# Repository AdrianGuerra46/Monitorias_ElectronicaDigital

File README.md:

# Monitoria Electrónica Digital 

### Docente: Yeison Montagut 

Seré el monitor (también conocido como asistente de docencia) de electrónica digital, asignatura de Séptimo semestre de Ingeniería Mecatrónica en la Universidad EIA. 

Mi responsabilidad directa será dar asesoria a los estudiantes en los eventos calificables los cuales son: exámenes (dos(2) quices, parcial y final) y los 3 últimos de los 4 laboratorios de la asignatura (no ayudaré de manera directa en el laboratorio 1 por solicitud del docente) aún asi, daré apoyo extra a los estudiantes si es necesario.  

***Aclaración:*** El equipo que uso para desarrollar todas las tareas funciona con el sistema operativo Windows. Por esta razón todo el desarrollo del repositorio y las diferentes recomendaciones estarán hechas desde mi experiencia abordando todo con Windows. AUN ASÍ el proceso no cambia en prácticamente nada desde otros sistemas operativos.
> **NOTA:** El objetivo del repositorio **NO** es exponer y explicar todo el temario de la asignatura. El objetivo es exponer la solución de los entregables y los diferentes desarrollos que llevé a cabo para poder afrontar mi rol de monitor de la mejor manera posible. 

#### Desarrollo de la asignatura 

De forma **muy general** la asignatura se divide principalmente en dos temas, los cuales están divididos cronológicamente por el examen parcial.

1. [**Pre-Parcial**](https://github.com/AdrianGuerra46/Monitorias_ElectronicaDigital/tree/main/Pre-Parcial): En esta primera parte tenemos el primer acercamiento a la electrónica digital trantando temas como:
    - Sistemas numéricos 
    - Compuertas lógicas
    - FPGA (Basys 3)
    - VHDL (Vivado)
    - Entre otros. 

    Esta primera parte incluye los siguientes eventos calificables:

    - Laboratorio 1: Primer acercamiento con la tarjeta Basys 3 y comprobación práctica de las compuertas lógicas usando el lenguaje VHDL y el software Vivado. 
    - Quiz 1: Enfocado en Compuertas lógicas y aplicación sobre la tarjeta Basys 3 usando VHDL.
    - Laboratorio 2: Diseñar e implementar sistemas digitales basado en lógica secuencial en una FPGA.
    - Parcial: Es la segunda evaluación más significativa del curso (con una valor del 20%) y se evaua todo el conocimiento tanto conceptual como práctico obtenido hasta el momento. 
2. [**Post-Parcial:**](https://github.com/AdrianGuerra46/Monitorias_ElectronicaDigital/tree/main/Post-Parcial) En esta segunda parte del curso nos enfocamos en microcontroladores y se abordan temas como: 
    - Introducción a los microcontroladores (Qué es?, Partes, entre otros.).
    - ESP32 (Principal microcontrolador de la asignatura) 
    - Visual Studio Code 
    - Manejo de Puertos
    - Sensores
    - Entre otros.

    En esta segunda parte de la asignatura tendremos los siguientes eventos calificables:
    - Laboratorio 3: Diseñar e implementar una aplicación básica en un microcontrolador ESP32.
    - Quiz 2: Enfocado en la programación de microncotroladores, trabajando sobre VSCode
    - Laboratorio 4: Implementar una aplicación completa sobre el microcontrolador ESP32. 
    - Final: Examen más importante de la asignatura (con un valor del 30%) donde se evaluará todo el conocimiento adquirido durante la asignatura aunque, enfocado principalmente en los temas Post-Parcial.

Cada uno de estos temas estarám mejor abordados en sus respectivos directorios

### Estructura del repositorio

- En el repositorio montaré todo lo que tenga que resolver/desarrollar durante el proceso de la monitoria, es decir, talleres, laboratorios, entre otros. 
- Dividiré el temario y desarrollo en dos directorios, Pre-Parcial y Post-Parcial. En los cuales abordaré todo los diseños y soluciones. Estarán divididos en tantos directorios y ficheros como considere necesarios (esto estará mejor explicado en el archivo README de cada directorio).
- A su vez, estos directorios estarán divididos en otros directorios los cuales estarán enumerados de forma cronológica (para ser abordados de la misma manera). En estos se encontrarán tanto enunciados como soluciones de cada Taller, Quiz, Laboratorio, Etc. 

> Nota: En algunos directorios puede que haya algunos archivos PDF provenientes de mi Tablet (dispositivo donde tomo apuntes) estos serán incluidos si condero necesario para realizar anotaciones o desarrolos más explicitos y dejar mejor explicado el tema o el el proceso de diseño de cada entregable. *De antemano me disculpo por mi letra y gráficos* :sweat_smile:

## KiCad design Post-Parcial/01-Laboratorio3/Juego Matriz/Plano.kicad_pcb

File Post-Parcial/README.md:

# Post-Parcial 

## Microcontroladores

La segunda mitad de la asignatura está enfocada principalmente en **microcontroladores**. El microcontrolador "rey de la asignatura" será el ESP32, sobre este desarrollaremos software para implementar en hardware. Programaremos en C y Arduino, para proximamente implementar en cirucitos haciendo uso desde led's hasta sensores y motores.

## Requisitos Previos

- **Visual Studio Code:** Visual Studio Code es un editor de código fuente desarrollado por Microsoft para Windows, Linux, macOS y Web. Este será nuestro editor de código en esta parte de la asignatura. Puedes descargarlo directamente desde su [sitio oficial](https://code.visualstudio.com/download).
    - PlatformIO: es una IDE abierta de programación para C/C++, orientado al hardware. ¿Qué es una IDE? Es una sigla y acrónimo en inglés de integrated development environment, en español es un conjunto de herramientas para desarrollo (programación) generalmente agrupadas en una misma interfaz gráfica. Este será el IDE que usaremos para programar el ESP32 tanto en C como en Arduino. Puedes decargarlo desde la interfaz de extensiones de Visual Studio Code. 

- **Driver:** Según mi experiencia algunos equipos pueden tener problemas para reconocer el ESP32. Esto puedes verlo accediendo al administrador de dispositivos e identificando un simbolo de exclamación sobre un dispositivo USB.
  
  Si ese llega a ser tu caso, puedes descargar el driver desde [Este enlace](https://www.silabs.com/developers/usb-to-uart-bridge-vcp-drivers?tab=downloads) Te recomiendo la versión "Universal Windows Driver" (Si estas trabajando desde Windows). E instalarlo dandole a "actualizar controlador" y buscando la carpeta donde descargaste el controlador.
- **Proteus:** Proteus es el programa con el que se realizarán algunas simulaciones de los circuitos electrónicos, procedimiento el cual siempre es recomendado antes de montar directaremente los componentes.
- **KiCad8:** Este es mi programa preferido para realizar esquematicos y migrarlos a PCB, y por esta razón lo usaré para realizar los esquematicos que considere necesarios (En la asignatura no se aborda directamente el diseño de PCB ni el uso de este software, esto es puramente elección personal). Puedes descargarlo desde su [página oficial](https://www.kicad.org/download/).

## Conceptos 

### ¿Qué es un microcontrolador?

Un microcontrolador (abreviado µC, UC o mCU) es un circuito integrado programable, capaz de ejecutar las órdenes grabadas en su memoria. Está compuesto de varios bloques funcionales que cumplen una tarea específica. Un microcontrolador incluye en su interior las tres principales unidades funcionales de una computadora: unidad central de procesamiento, memoria y periféricos de entrada/salida.

### ESP32

ESP32 es la denominación de una familia de chips SoC de bajo coste y consumo de energía, con tecnología Wi-Fi y Bluetooth de modo dual integrada. El ESP32 emplea un microprocesador Tensilica Xtensa LX6 en sus variantes de simple y doble núcleo e incluye interruptores de antena, balun de radiofrecuencia, amplificador de potencia, amplificador receptor de bajo ruido, filtros, y módulos de administración de energía. El ESP32 fue creado y desarrollado por Espressif Systems y es fabricado por TSMC utilizando su proceso de 40 nm.Este será nuestra principal herramienta de trabajo en esta segunda y última parte del curso.

##### Distribución de Pinout de ESP32

Esta imagen será muy importante para el desarrollo de todos los sistemas asociados a este microncontrolador.

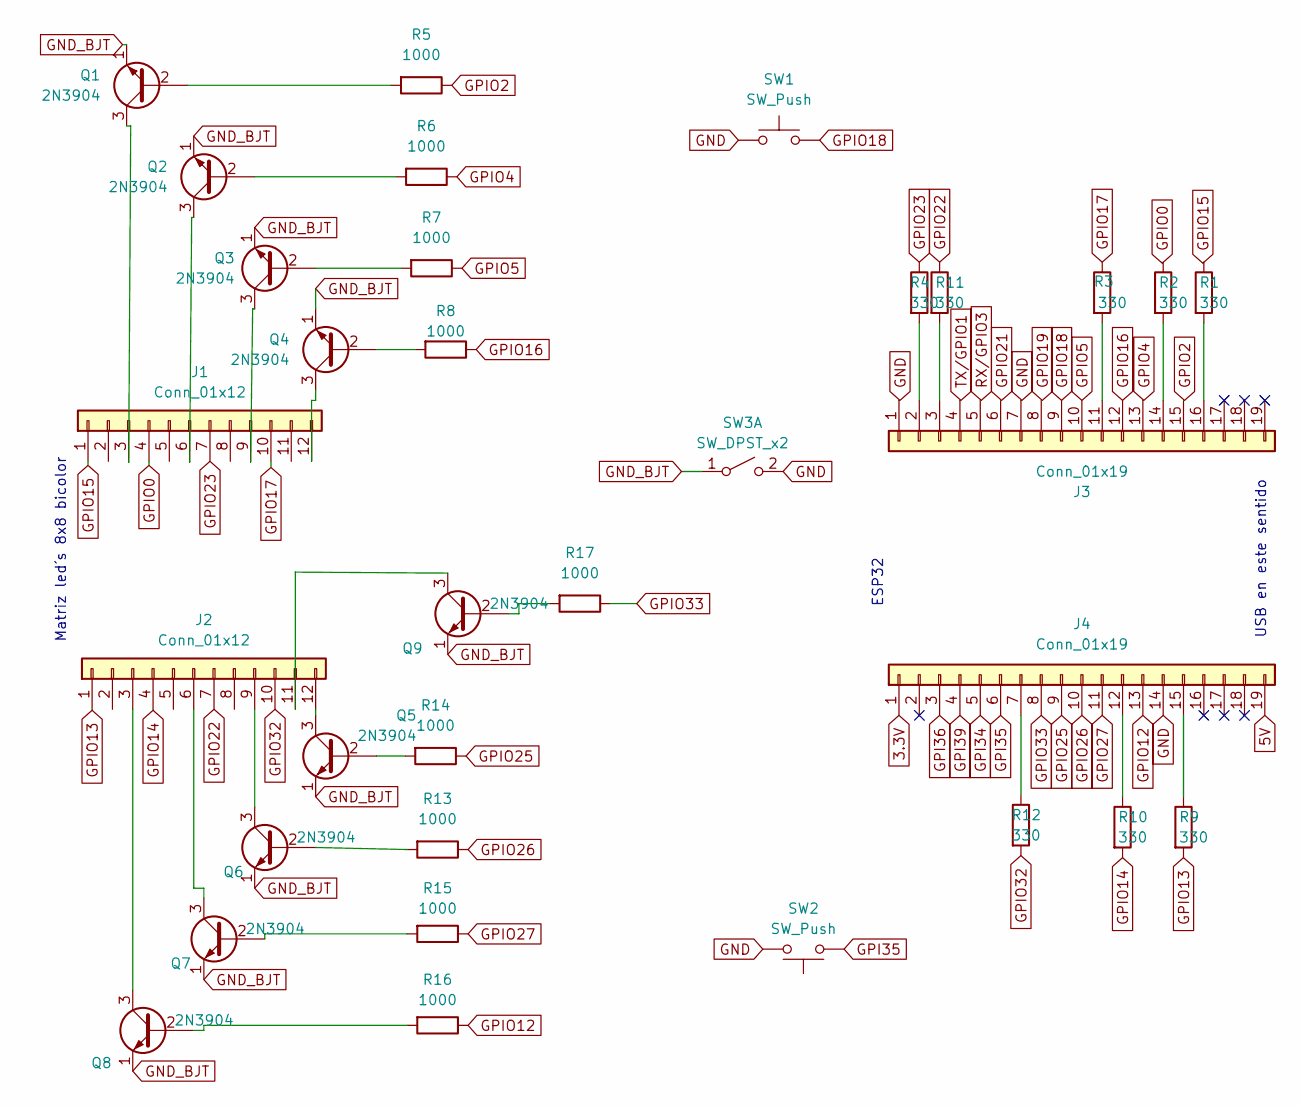
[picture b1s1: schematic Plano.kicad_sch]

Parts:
J1, J2: Conn_01x12; PinSocket_1x12_P2.54mm_Vertical
J3, J4: Conn_01x19; PinSocket_1x19_P2.54mm_Vertical
Q1, Q2, Q3, Q4, Q5, Q6, Q7, Q8, Q9: 2N3904; PinSocket_1x03_P2.54mm_Vertical
R1, R2, R3, R9, R10: 330; R_Axial_DIN0309_L9.0mm_D3.2mm_P2.54mm_Vertical
R4, R11, R12: 330; R_Axial_DIN0207_L6.3mm_D2.5mm_P10.16mm_Horizontal
R5, R6, R7, R8, R14, R15, R16, R17: 1000; R_Axial_DIN0309_L9.0mm_D3.2mm_P2.54mm_Vertical
R13: 1000; R_Axial_DIN0207_L6.3mm_D2.5mm_P10.16mm_Horizontal
SW1, SW2: SW_Push; SW_DIP_SPSTx01_Piano_10.8x4.1mm_W7.62mm_P2.54mm
SW3: SW_DPST_x2; SW_DIP_SPSTx01_Slide_6.7x4.1mm_W7.62mm_P2.54mm_LowProfile

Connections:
3.3V: J4.1
5V: J4.19
GND: J3.1, J3.7, J4.14, SW1.1, SW2.2, SW3.2 (B)
GND_BJT: Q1.1 (E), Q2.1 (E), Q3.1 (E), Q4.1 (E), Q5.1 (E), Q6.1 (E), Q7.1 (E), Q8.1 (E), Q9.1 (E), SW3.1 (A)
GPI34: J4.5
GPI35: J4.6, SW2.1
GPI36: J4.3
GPI39: J4.4
GPIO0: J1.4, R2.1
GPIO2: J3.15, R5.1
GPIO4: J3.13, R6.1
GPIO5: J3.10, R7.1
GPIO12: J4.13, R16.1
GPIO13: J2.1, R9.2
GPIO14: J2.4, R10.2
GPIO15: J1.1, R1.1
GPIO16: J3.12, R8.1
GPIO17: J1.10, R3.1
GPIO18: J3.9, SW1.2
GPIO19: J3.8
GPIO21: J3.6
GPIO22: J2.7, R11.1
GPIO23: J1.7, R4.1
GPIO25: J4.9, R14.1
GPIO26: J4.10, R13.1
GPIO27: J4.11, R15.1
GPIO32: J2.10, R12.2
GPIO33: J4.8, R17.1
unnamed: J1.3, Q1.3 (C)
unnamed: J1.6, Q2.3 (C)
unnamed: J1.9, Q3.3 (C)
unnamed: J1.12, Q4.3 (C)
unnamed: J2.3, Q8.3 (C)
unnamed: J2.6, Q7.3 (C)
unnamed: J2.9, Q6.3 (C)
unnamed: J2.11, Q9.3 (C)
unnamed: J2.12, Q5.3 (C)
unnamed: J3.2, R4.2
unnamed: J3.3, R11.2
unnamed: J3.11, R3.2
unnamed: J3.14, R2.2
unnamed: J3.16, R1.2
unnamed: J4.7, R12.1
unnamed: J4.12, R10.1
unnamed: J4.15, R9.1
unnamed: Q1.2 (B), R5.2
unnamed: Q2.2 (B), R6.2
unnamed: Q3.2 (B), R7.2
unnamed: Q4.2 (B), R8.2
unnamed: Q5.2 (B), R14.2
unnamed: Q6.2 (B), R13.2
unnamed: Q7.2 (B), R15.2
unnamed: Q8.2 (B), R16.2
unnamed: Q9.2 (B), R17.2
RX/GPIO3: J3.5
TX/GPIO1: J3.4

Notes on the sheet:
USB en este sentido
ESP32
Matriz led´s 8x8 bicolor

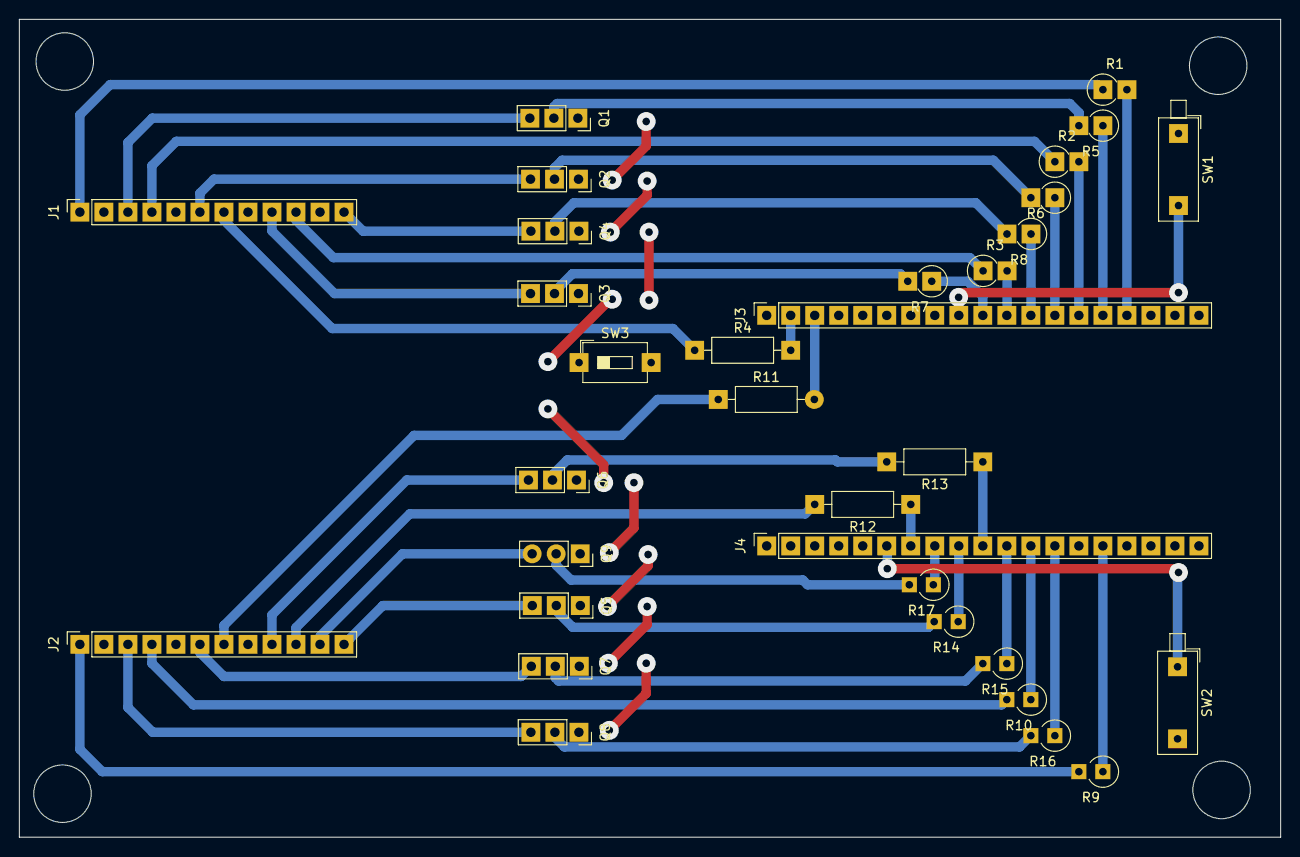
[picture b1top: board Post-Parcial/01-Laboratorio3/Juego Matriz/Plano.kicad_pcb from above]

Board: 2 copper layers, 133.4 x 86.5 mm, 33 parts (0 on the bottom side), 47 nets.

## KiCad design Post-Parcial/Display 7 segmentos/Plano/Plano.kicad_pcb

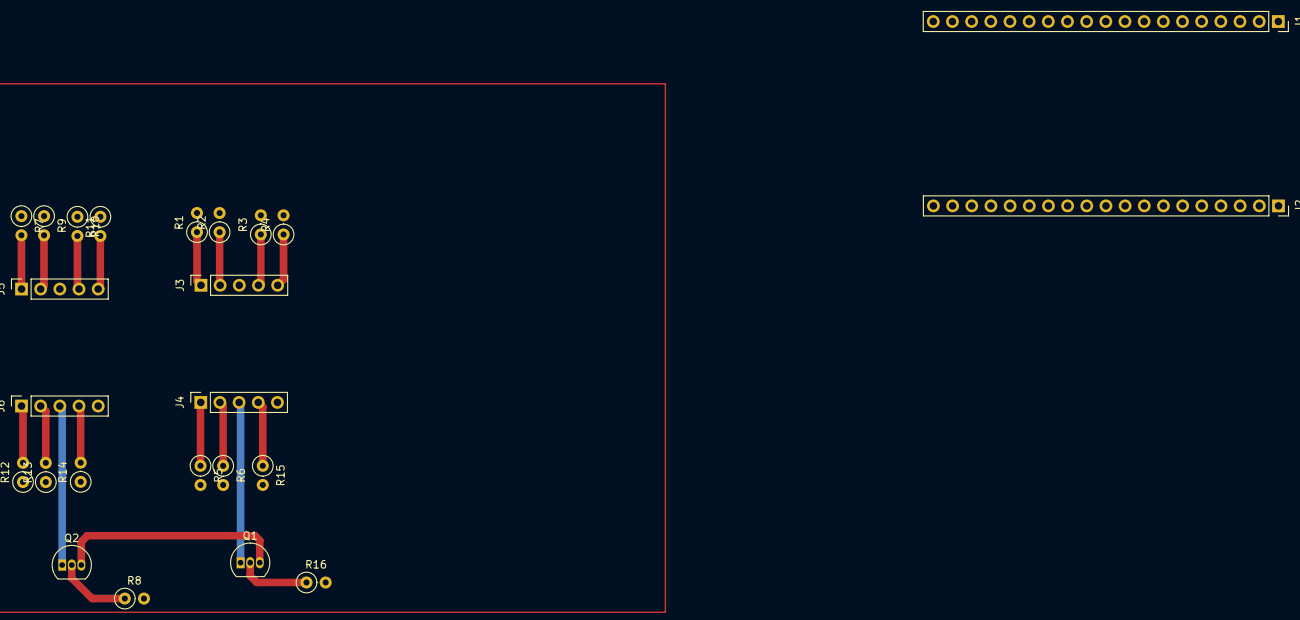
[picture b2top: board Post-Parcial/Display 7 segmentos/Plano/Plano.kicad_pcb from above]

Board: 2 copper layers, 24 parts (0 on the bottom side), 35 nets.

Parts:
J1, J2: Conn_01x19; PinSocket_1x19_P2.54mm_Vertical
J3, J4, J5, J6: Conn_01x05; PinSocket_1x05_P2.54mm_Vertical
Q1, Q2: 2N3904; TO-92_Inline
R1, R2, R3, R4, R5, R6, R7, R9, R10, R11, R12, R13, R14, R15: 330; R_Axial_DIN0207_L6.3mm_D2.5mm_P2.54mm_Vertical
R8, R16: 1000; R_Axial_DIN0207_L6.3mm_D2.5mm_P2.54mm_Vertical

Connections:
5V: J1.19, Q1.3 (C), Q2.3 (C)
GPIO1: J5.4, R10.2
GPIO3: J5.5, R11.2
GPIO9: J1.16, R16.2
GPIO12: J4.4, R15.1
GPIO13: J1.15, R8.2
GPIO14: J4.2, R6.1
GPIO18: J6.4, R14.2
GPIO19: J6.2, R13.2
GPIO21: J6.1, R12.2
GPIO22: J5.2, R9.2
GPIO23: J5.1, R7.2
GPIO25: J3.4, R3.1
GPIO26: J3.5, R4.1
GPIO27: J4.1, R5.1
GPIO32: J3.1, R1.1
GPIO33: J3.2, R2.1
unnamed: J1.7, R1.2
unnamed: J1.8, R2.2
unnamed: J1.9, R3.2
unnamed: J1.10, R4.2
unnamed: J1.11, R15.2
unnamed: J1.12, R6.2
unnamed: J1.13, R5.2
unnamed: J2.2, R7.1
unnamed: J2.3, R9.1
unnamed: J2.4, R10.1
unnamed: J2.5, R11.1
unnamed: J2.6, R12.1
unnamed: J2.8, R13.1
unnamed: J2.9, R14.1
unnamed: J4.3, Q1.1 (E)
unnamed: J6.3, Q2.1 (E)
unnamed: Q1.2 (B), R16.1
unnamed: Q2.2 (B), R8.1

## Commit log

2024-02-24 Carpeta de Documentos
2024-02-24 Documentos de monitor
2024-02-25 Actualización de Readme y reorganizacion del repo
2024-02-25 Actualización de Readme y añadí directorios
2024-02-25 Pruebas
2024-02-25 Actualizacion Readme
2024-02-25 Tutorial 1 Finalizado
2024-02-26 Creacion de directorio para tuto 2
2024-02-26 Tuto 2 Finalizado
2024-02-26 Actualización PARCIAL de la estructura del repo
2024-02-27 Cambio en la estrcutura del repo
2024-02-27 Finalización de readme
2024-02-27 error
2024-02-27 Actualizacion readme principal
2024-02-27 Finalizacion de Readme´s
2024-03-01 Avance KiCad Juego
2024-03-01 Migracion a Kicad8
2024-03-01 Finalizacion PCB Juego
2024-03-01 Proyecto para perfeccionar la PCB
2024-03-01 Cambios en Prueba PCB Juego
2024-03-02 Prueba Juego Terminada
2024-03-02 PCB Juego Finalizado
2024-03-02 Version Final PCB Matriz Leds
2024-03-06 Reorganización de PCB Juego Matriz
2024-03-06 Avance nueva PCB juego matriz
2024-03-06 PCB Juego Finalizada
2024-03-07 Añadi Agujeros a la placa
2024-03-09 Simulación del primer punto taller quiz 1
2024-03-09 Actualizacion de Readme añadiendo Proteus
2024-03-13 Inicializacion de Carpeta Pre Parcial
2024-03-13 Primer Punto terminado. Datasheets añadidos
2024-03-20 Avance taller pre parcial
2024-04-10 Actualizacíon vuelta break
2024-04-26 Documentos quiz 2
2024-04-27 Terminado Ejemplo 4 e inicio de Ejemplo 3
2024-04-27 Ejemplos finalizados
2024-04-28 Actualizaciones de README's y añadido de algunos archivos
2024-04-30 Cambio de estructura
2024-04-30 Avance en Circuito Ejemplos
2024-05-09 Avance en directorio PostParcial
2024-05-17 Reorganizacion de Directorios
2024-05-17 Primer Ejemplo Arduino Terminado
2024-05-18 Ejemplos de Arduino Terminados
2024-05-22 Repositorio PreFinal
2024-06-04 Semestre de Monitoria Finalizado
2024-06-04 Cierre de Semestre
2024-07-21 Simulación hasta punto 7 taller quiz 1
2024-07-22 Simulaciones taller quiz 1 finalizadas
2024-08-02 new directory basys
2024-08-10 first monitoria quiz 1
2024-08-10 Eliminated
2024-08-11 First Try Quiz 1
2024-08-30 Pre parcial
2024-09-06 06/09/2024
2024-09-18 18/09/2024
2024-11-16 16/11/2024
2025-07-20 Formateo 20/07
